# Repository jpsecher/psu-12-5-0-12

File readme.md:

# Linear power supply +12V +5V 0V -12V

For eg. a Eurorack modular synth.

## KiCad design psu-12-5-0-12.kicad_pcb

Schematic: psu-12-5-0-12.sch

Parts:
C1, C2: 4m7; CP_Axial_L42.5mm_D20.0mm_P49.00mm_Horizontal
C3: 330n; C_Rect_L11.0mm_W4.2mm_P10.00mm_MKT
C4: 2µ2 tant; CP_Axial_L11.0mm_D5.0mm_P18.00mm_Horizontal
C5, C8: 100n; C_Rect_L9.0mm_W2.5mm_P7.50mm_MKT
C6: 1µ; CP_Axial_L11.0mm_D5.0mm_P18.00mm_Horizontal
C7: 22µ tant; CP_Radial_Tantal_D6.0mm_P5.00mm
D1: -AA+; Diode_Bridge_32.0x5.6x17.0mm_P10.0mm_P7.5mm
D2: LED; LED_D5.0mm_FlatTop
D3: 1N4001; D_A-405_P10.16mm_Horizontal
D4, D5: BYV10; D_A-405_P7.62mm_Horizontal
J1: 12/0/12VAC; TerminalBlock_bornier-3_P5.08mm
J2: 5/12/0/-12VDC; TerminalBlock_bornier-4_P5.08mm
R2: 3k9; R_Axial_DIN0207_L6.3mm_D2.5mm_P10.16mm_Horizontal
U1: L7812; TO-220-3_Vertical
U2: L7912; TO-220-3_Vertical
U3: L7805; TO-220-3_Vertical

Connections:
/+5V: C8.1, J2.1, U3.3
/+12V: C5.1, D3.2, D4.1, J2.2, U1.3 (OUT)
/-12V: C6.2, D5.2, J2.4, U2.3 (VO)
/GND: C1.2, C2.1, C3.2, C4.1, C5.2, C6.1, C7.2, C8.2, D4.2, D5.1, J1.2, J2.3, U1.2 (GND), U2.1 (GND), U3.2
unnamed: C1.1, C3.1, D1.4, R2.1, U1.1 (IN)
unnamed: C2.2, C4.2, D1.1, D2.1, U2.2 (VI)
unnamed: C7.1, D3.1, U3.1
unnamed: D1.2, J1.3
unnamed: D1.3, J1.1
unnamed: D2.2, R2.2

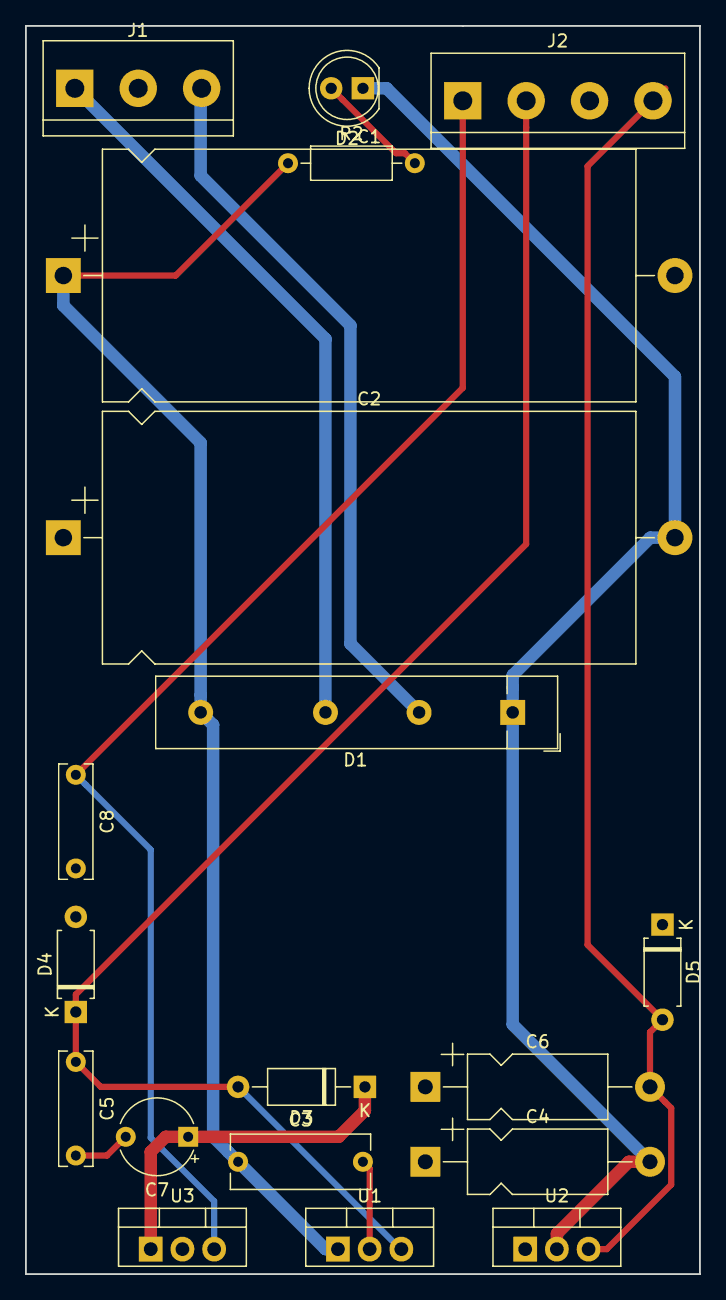
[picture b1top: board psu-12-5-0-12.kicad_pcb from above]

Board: 2 copper layers, 54.0 x 100.0 mm, 19 parts (0 on the bottom side), 10 nets.

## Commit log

2019-01-12 Schematic.
2019-01-12 Footprints.
2019-01-14 WIP: PCB fiddling.
